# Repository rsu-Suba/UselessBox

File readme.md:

## メインファイル
- コード [ONOFF_V2](./ONOFF_V4/ONOFF_V4.ino)
- 回路画像 [OnOffBread.png](./OnOffBread.PNG.png)
- PCB画像(不使用) [OnOff.brd](./OnOff2.brd)
- 3Dモデル(Ver2) [OnOff3D.f3d](./OnOff3D.f3d)
---
### 2020年

### 2月
製作開始 (2/8/2020)  
Ver1 (2/11/2020)
- Arduino Uno 3
- 蓋サーボとスイッチサーボが同じアーム  
- すべてアクリル板  
- 電池単1.5*2  

### 3月

Ver2 (3/2/2020)
- Arduino Nano Every
- 蓋サーボとスイッチサーボを分離
- すべてアクリル板
- 電池9V*1

Ver3 (3/12/2020)
- Arduino Nano Every
- Ver2の改良版
- 基盤、配線、スイッチ、マイコンを一つの基盤に移植
- すべてアクリル板
- 電池9V : 1 | 1.5V : 4

### 4～5月
アルミ土台を設計

### 7月
Ver4 (7/19/2020)
- Arduino Pro Mini
- リセットボタン、RGBLED追加
- サーボのスピード変更可にした
- アルミ土台、外側だけアクリル板
- 電池9V : 1 | 1.5V : 4
---
### 2021年

### 10月
16x8ドットマトリクステスト

---
#### Inspired by [全力でスイッチをONするとOFFするロボットと戦ってみた](https://youtu.be/bOD2-mRphTI)

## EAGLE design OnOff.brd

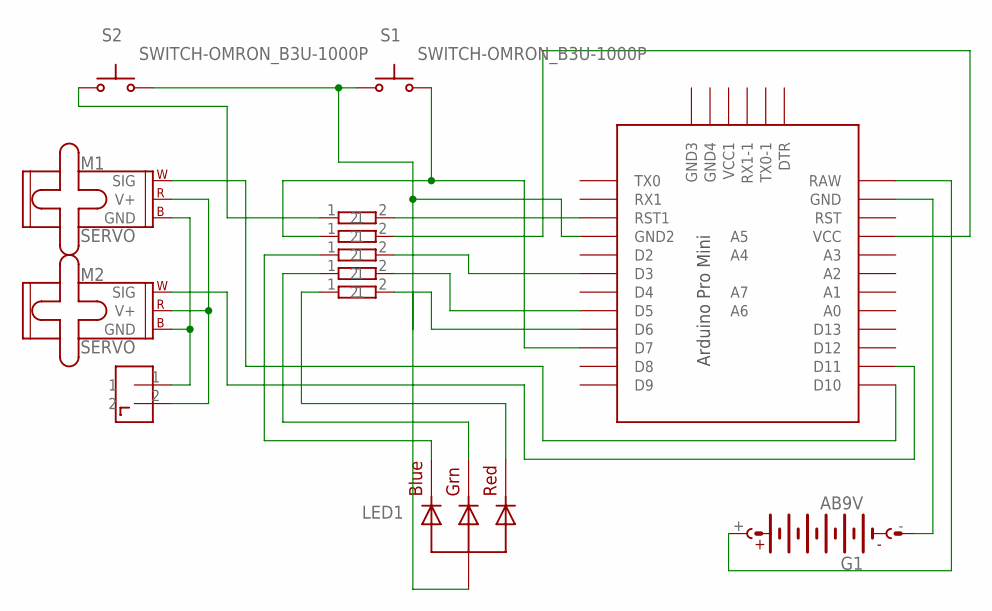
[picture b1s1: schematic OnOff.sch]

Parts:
CONNECTOR1: 2PIN
CONNECTOR2, CONNECTOR3, CONNECTOR4, CONNECTOR5, CONNECTOR6: RESISTER; RESISTER_SOCKET
G1: AB9V
LED1: RGBLED_CA-5MM; LED5MMRGB
M1, M2: SERVO; 1X03
S1, S2: SWITCH-OMRON_B3U-1000P
U$1: PRO-MINI-2

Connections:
unnamed: G1.-, U$1.GND
unnamed: G1.+, U$1.RAW
unnamed: CONNECTOR1.1, M1.3 (GND), M2.3 (GND)
unnamed: CONNECTOR1.2, M1.2 (V+), M2.2 (V+)
unnamed: CONNECTOR4.1, LED1.4 (BLUE)
unnamed: CONNECTOR5.1, LED1.3 (GREEN)
unnamed: CONNECTOR6.1, LED1.1 (RED)
unnamed: CONNECTOR6.2, U$1.D6
unnamed: CONNECTOR5.2, U$1.D5
unnamed: CONNECTOR4.2, U$1.D3
unnamed: CONNECTOR3.1, S1.2 (S), U$1.D7
unnamed: CONNECTOR2.2, U$1.RST1
unnamed: CONNECTOR2.1, S2.1
unnamed: M2.1 (SIG), U$1.D11
unnamed: M1.1 (SIG), U$1.D10
unnamed: LED1.2 (VCC), S1.1, S2.2 (S), U$1.GND1 (GND2)
unnamed: CONNECTOR3.2, U$1.VCC

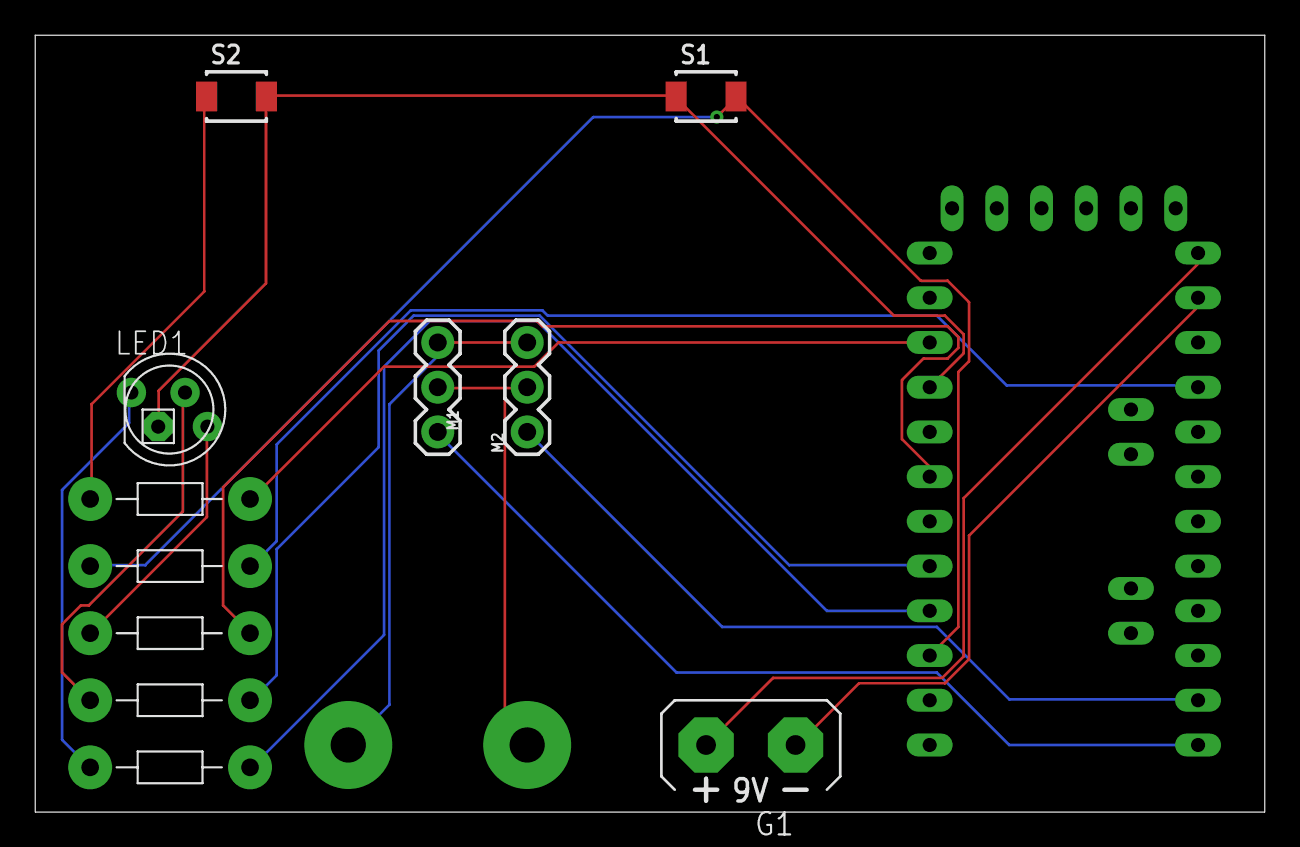
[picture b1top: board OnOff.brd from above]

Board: 2 copper layers, 69.8 x 44.1 mm, 13 parts (0 on the bottom side), 17 nets.

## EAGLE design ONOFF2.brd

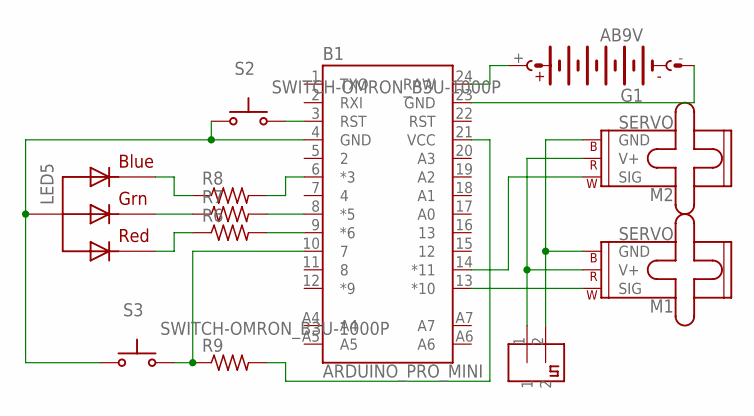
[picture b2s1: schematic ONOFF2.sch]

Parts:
B1: ARDUINO_PRO_MINI
CONNECTOR1: 2PIN
G1: AB9V
LED5: RGBLED_CA-5MM; LED5MMRGB
M1, M2: SERVO; 1X03
R6, R7, R8, R9: R-US_AXIAL-7.2MM-PITCH; RESAD724W46L381D178B
S2, S3: SWITCH-OMRON_B3U-1000P

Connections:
unnamed: B1.23 (GND), G1.-
unnamed: CONNECTOR1.2, M1.3 (GND), M2.3 (GND)
unnamed: B1.4 (GND), LED5.2 (VCC), S2.1, S3.1
unnamed: CONNECTOR1.1, M1.2 (V+), M2.2 (V+)
unnamed: B1.13 (*10), M1.1 (SIG)
unnamed: B1.14 (*11), M2.1 (SIG)
unnamed: LED5.4 (BLUE), R8.1
unnamed: LED5.3 (GREEN), R7.1
unnamed: LED5.1 (RED), R6.1
unnamed: B1.10 (7), R9.1, S3.2 (S)
unnamed: B1.9 (*6), R6.2
unnamed: B1.8 (*5), R7.2
unnamed: B1.6 (*3), R8.2
unnamed: B1.3 (RST), S2.2 (S)
unnamed: B1.21 (VCC), R9.2
unnamed: B1.24 (RAW), G1.+

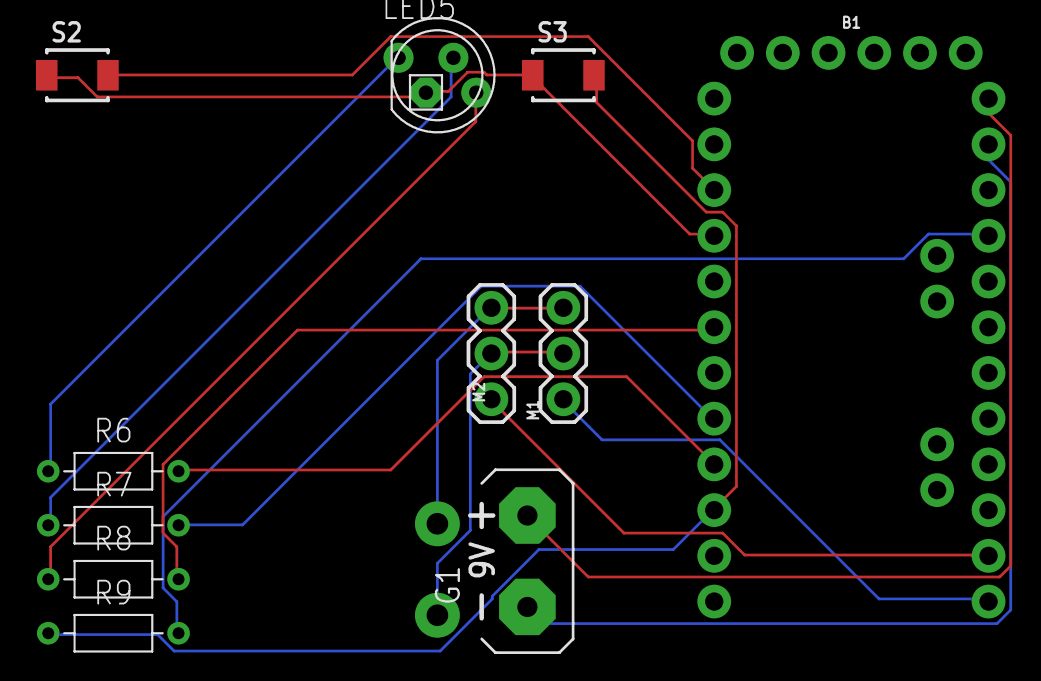
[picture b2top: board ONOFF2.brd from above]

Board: 2 copper layers, 12 parts (0 on the bottom side), 16 nets.

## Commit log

2026-03-23 Update 2026

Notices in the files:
parts and their libraries:
Arduino: Licensing: Creative Commons ShareAlike 4.0 International - https://creativecommons.org/licenses/by-sa/4.0
